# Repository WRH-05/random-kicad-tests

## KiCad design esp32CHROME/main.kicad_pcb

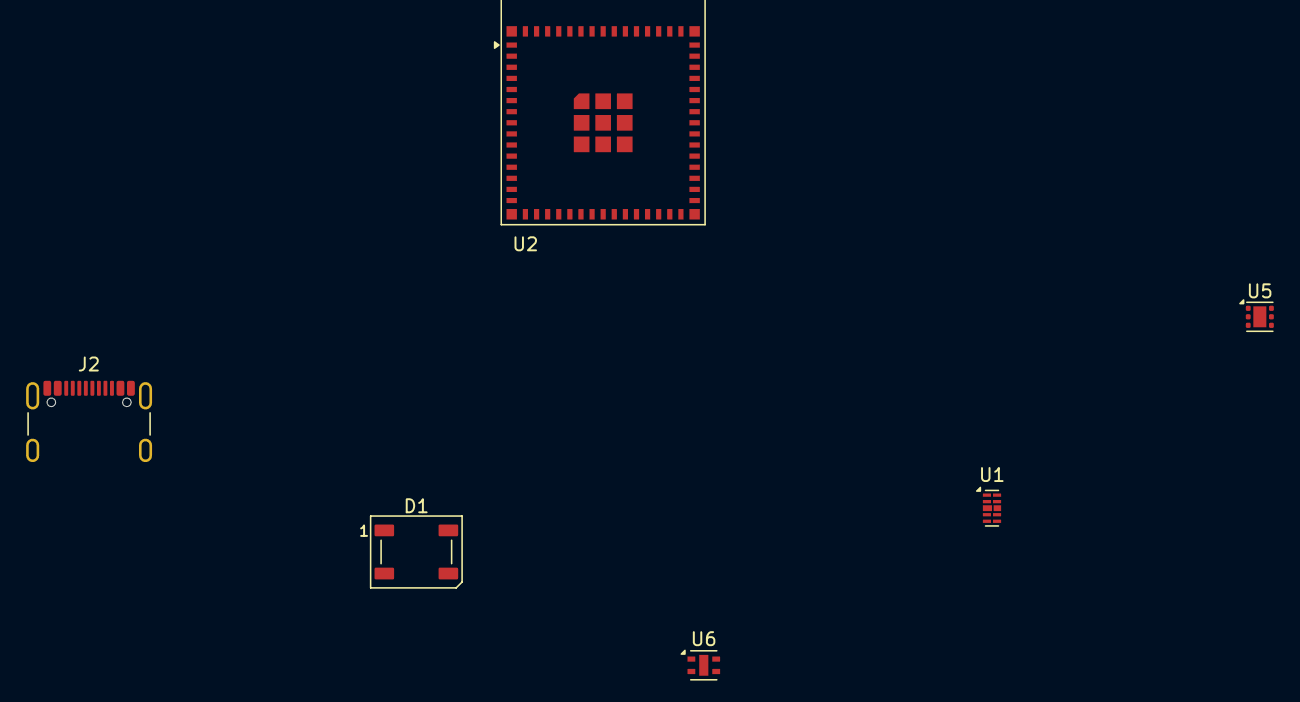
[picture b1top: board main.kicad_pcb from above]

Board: 2 copper layers, 6 parts (0 on the bottom side), 6 nets, no tracks yet.

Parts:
D1: WS2812B; LED_WS2812B_PLCC4_5.0x5.0mm_P3.2mm
J2: USB_C_Receptacle_USB2.0_16P; USB_C_Receptacle_GCT_USB4105-xx-A_16P_TopMnt_Horizontal
U1: D3V3XA4B10LP; Diodes_UDFN-10_1.0x2.5mm_P0.5mm
U2: ESP32-S3-MINI-1; ESP32-S2-MINI-1
U5: TLV75801PDRV; WSON-6-1EP_2x2mm_P0.65mm_EP1x1.6mm
U6: ENS210; AMS_QFN-4-1EP_2x2mm_P0.95mm_EP0.7x1.6mm

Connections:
unnamed: J2.A1 (GND), J2.A12 (GND), J2.B1 (GND), J2.B12 (GND)
unnamed: J2.A4 (VBUS), J2.A9 (VBUS), J2.B4 (VBUS), J2.B9 (VBUS)
unnamed: U1.3 (VSS), U1.8 (VSS)
unnamed: U2.1 (GND), U2.2 (GND), U2.42 (GND), U2.43 (GND), U2.46 (GND), U2.47 (GND), U2.48 (GND), U2.49 (GND), U2.50 (GND), U2.51 (GND), U2.52 (GND), U2.53 (GND), U2.54 (GND), U2.55 (GND), U2.56 (GND), U2.57 (GND), U2.58 (GND), U2.59 (GND), U2.60 (GND), U2.61 (GND), U2.62 (GND), U2.63 (GND), U2.64 (GND), U2.65 (GND)
unnamed: U5.3 (GND), U5.7 (GND)
unnamed: U6.4 (GND), U6.5 (GND)

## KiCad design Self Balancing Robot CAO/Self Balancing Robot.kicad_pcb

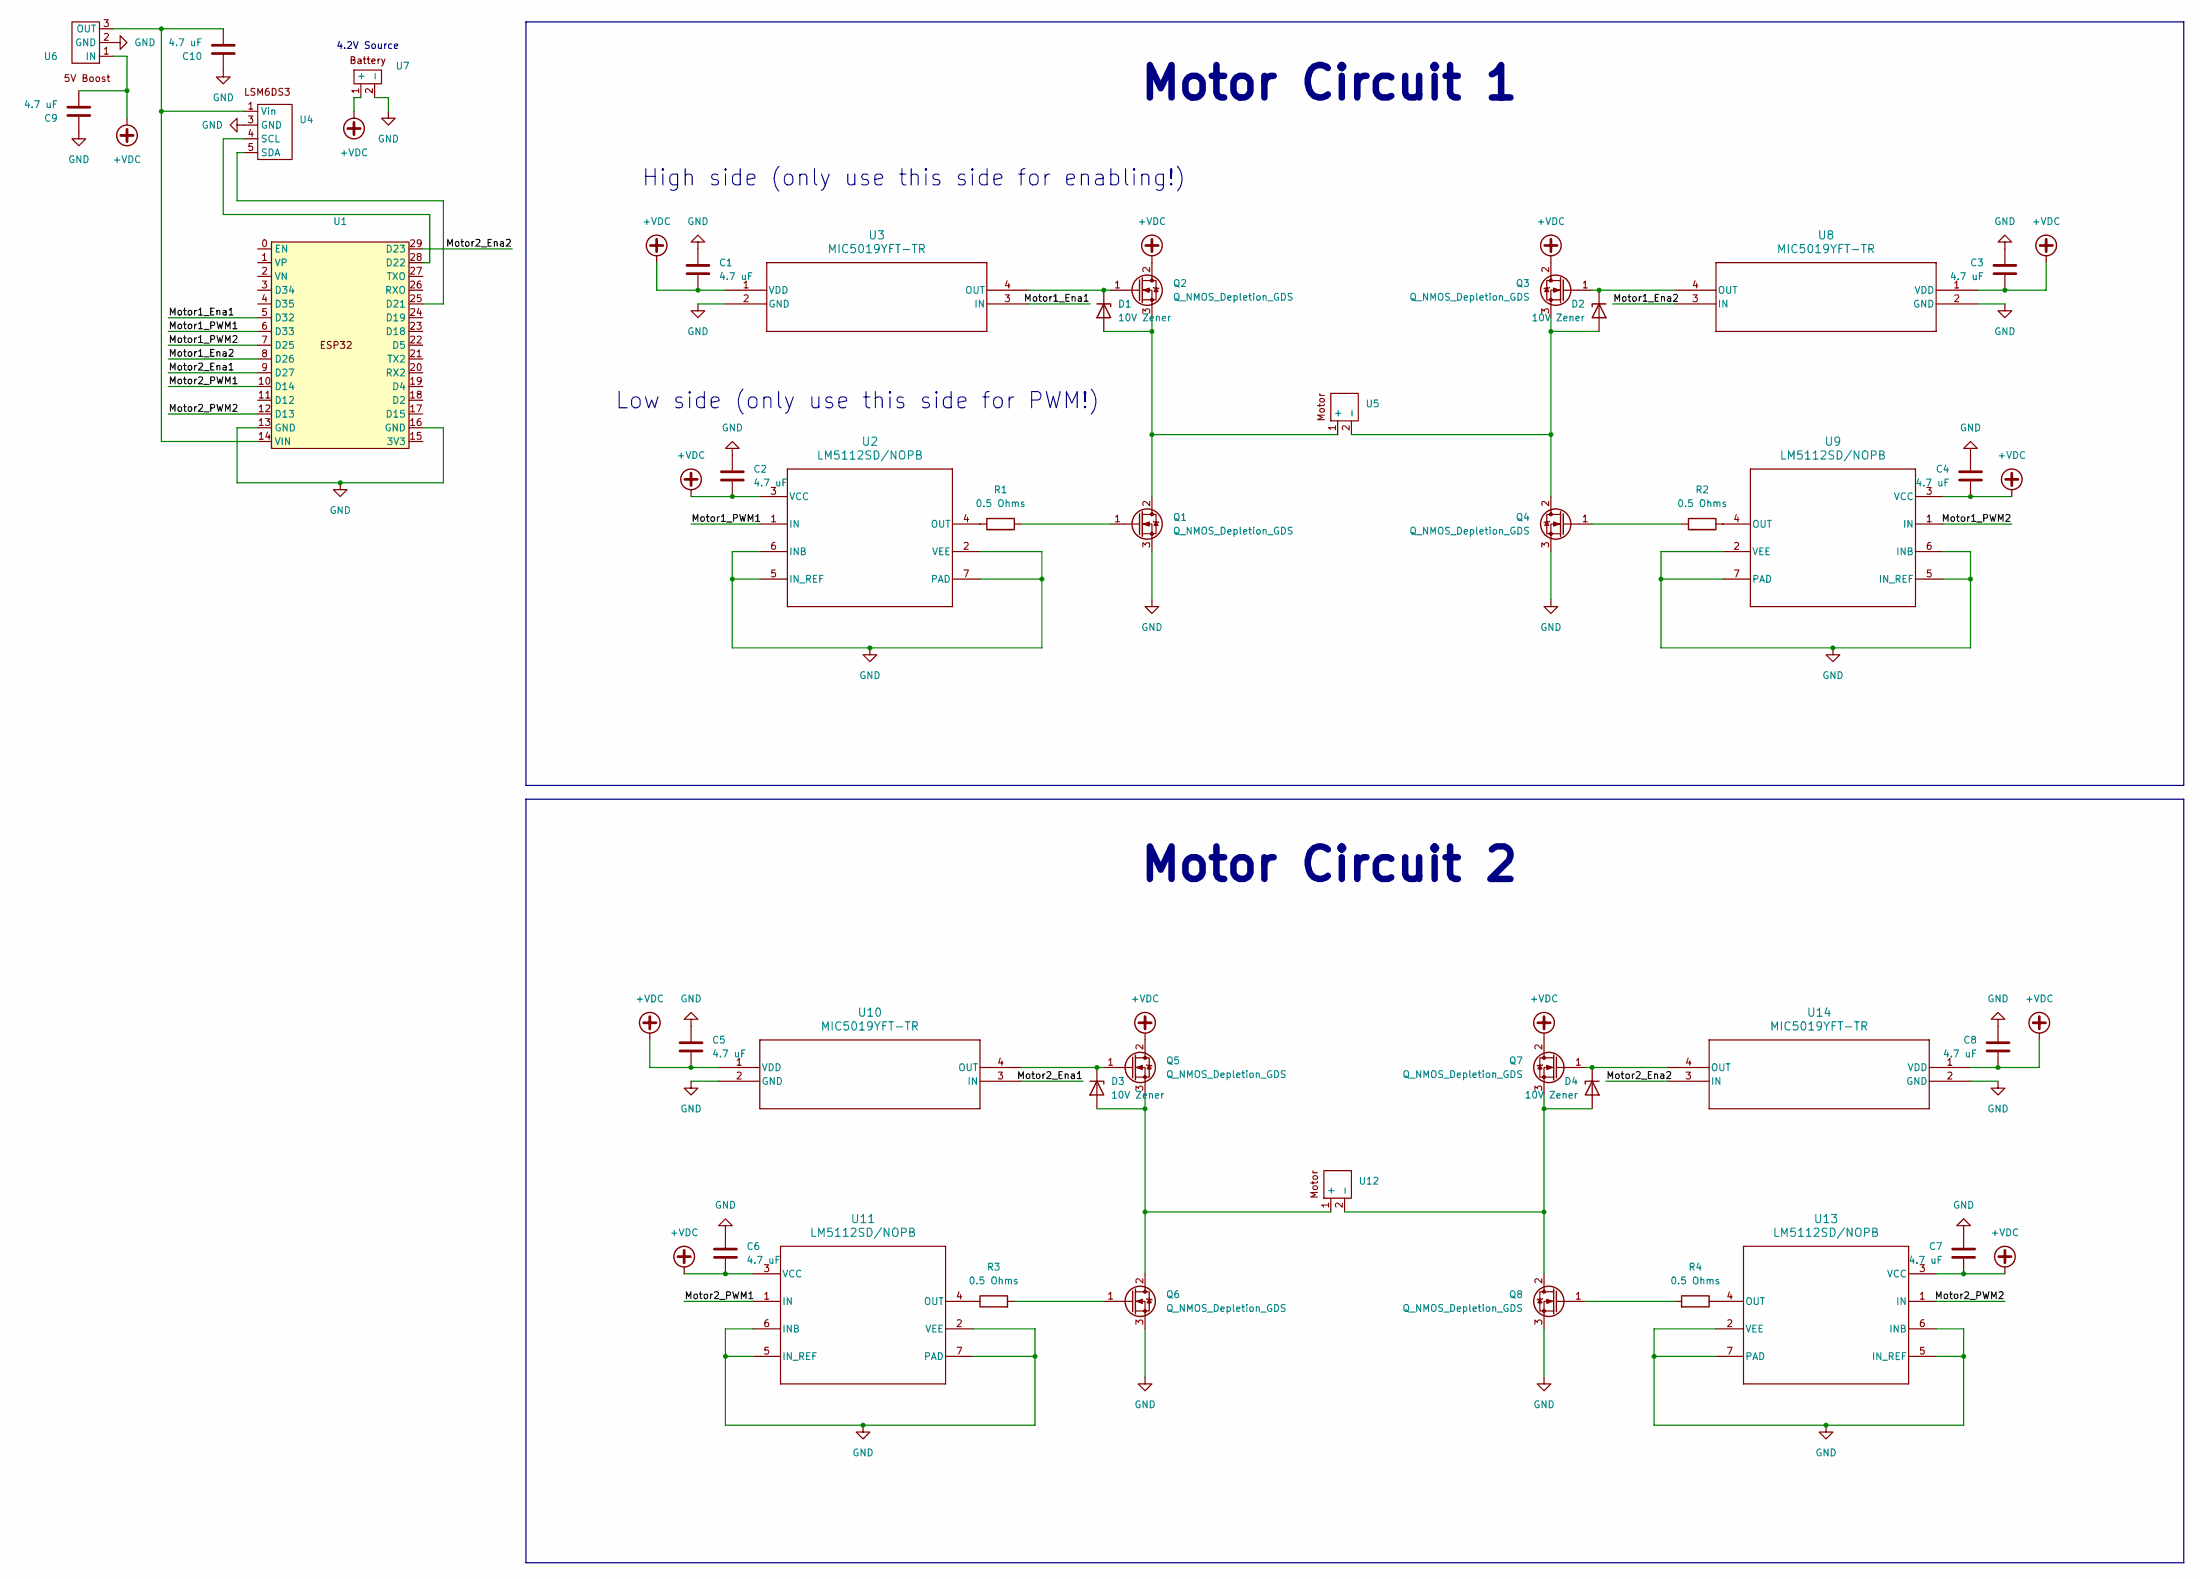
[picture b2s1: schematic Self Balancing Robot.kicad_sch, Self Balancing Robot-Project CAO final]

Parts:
C1, C2, C3, C4, C5, C6, C7, C8, C9, C10: 4.7 uF; C_0805_2012Metric_Pad1.18x1.45mm_HandSolder
D1, D2, D3, D4: 10V Zener; TSOT-23
Q1, Q2, Q3, Q4, Q5, Q6, Q7, Q8: Q_NMOS_Depletion_GDS; TO-252-2
R1, R2, R3, R4: 0.5 Ohms; R_2010_5025Metric_Pad1.40x2.65mm_HandSolder
U1: ESP32
U2, U9, U11, U13: LM5112SD/NOPB; LM5112SD
U3, U8, U10, U14: MIC5019YFT-TR
U4: LSM6DS3
U5, U12: Motor
U6: Boost
U7: Battery

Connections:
+VDC: C1.2, C2.2, C3.2, C4.2, C5.2, C6.2, C7.2, C8.2, C9.2, Q2.2 (D), Q3.2 (D), Q5.2 (D), Q7.2 (D), U2.3 (VCC), U3.1 (VDD), U6.1 (IN), U7.1 (+), U8.1 (VDD), U9.3 (VCC), U10.1 (VDD), U11.3 (VCC), U13.3 (VCC), U14.1 (VDD)
/Motor1_Ena1: U1.5 (D32), U3.3 (IN)
/Motor1_Ena2: U1.8 (D26), U8.3 (IN)
/Motor1_PWM1: U1.6 (D33), U2.1 (IN)
/Motor1_PWM2: U1.7 (D25), U9.1 (IN)
/Motor2_Ena1: U1.9 (D27), U10.3 (IN)
/Motor2_Ena2: U1.29 (D23), U14.3 (IN)
/Motor2_PWM1: U1.10 (D14), U11.1 (IN)
/Motor2_PWM2: U1.12 (D13), U13.1 (IN)
GND: C1.1, C2.1, C3.1, C4.1, C5.1, C6.1, C7.1, C8.1, C9.1, C10.1, Q1.3 (S), Q4.3 (S), Q6.3 (S), Q8.3 (S), U1.13 (GND), U1.16 (GND), U2.2 (VEE), U2.5 (IN_REF), U2.6 (INB), U2.7 (PAD), U3.2 (GND), U4.3 (GND), U6.2 (GND), U7.2 (-), U8.2 (GND), U9.2 (VEE), U9.5 (IN_REF), U9.6 (INB), U9.7 (PAD), U10.2 (GND), U11.2 (VEE), U11.5 (IN_REF), U11.6 (INB), U11.7 (PAD), U13.2 (VEE), U13.5 (IN_REF), U13.6 (INB), U13.7 (PAD), U14.2 (GND)
unnamed: D1.1 (A), Q1.2 (D), Q2.3 (S), U5.1 (+)
unnamed: D1.3 (K), Q2.1 (G), U3.4 (OUT)
unnamed: D2.1 (A), Q3.3 (S), Q4.2 (D), U5.2 (-)
unnamed: D2.3 (K), Q3.1 (G), U8.4 (OUT)
unnamed: D3.1 (A), Q5.3 (S), Q6.2 (D), U12.1 (+)
unnamed: D3.3 (K), Q5.1 (G), U10.4 (OUT)
unnamed: D4.1 (A), Q7.3 (S), Q8.2 (D), U12.2 (-)
unnamed: D4.3 (K), Q7.1 (G), U14.4 (OUT)
unnamed: Q1.1 (G), R1.2
unnamed: Q4.1 (G), R2.2
unnamed: Q6.1 (G), R3.2
unnamed: Q8.1 (G), R4.2
unnamed: U1.25 (D21), U4.5 (SDA)
unnamed: U1.28 (D22), U4.4 (SCL)
unnamed: C10.2, U1.14 (VIN), U4.1 (Vin), U6.3 (OUT)
unnamed: R1.1, U2.4 (OUT)
unnamed: R2.1, U9.4 (OUT)
unnamed: R3.1, U11.4 (OUT)
unnamed: R4.1, U13.4 (OUT)

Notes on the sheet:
4.2V Source
Motor Circuit 2
Motor Circuit 1
High side (only use this side for enabling!)
Low side (only use this side for PWM!)

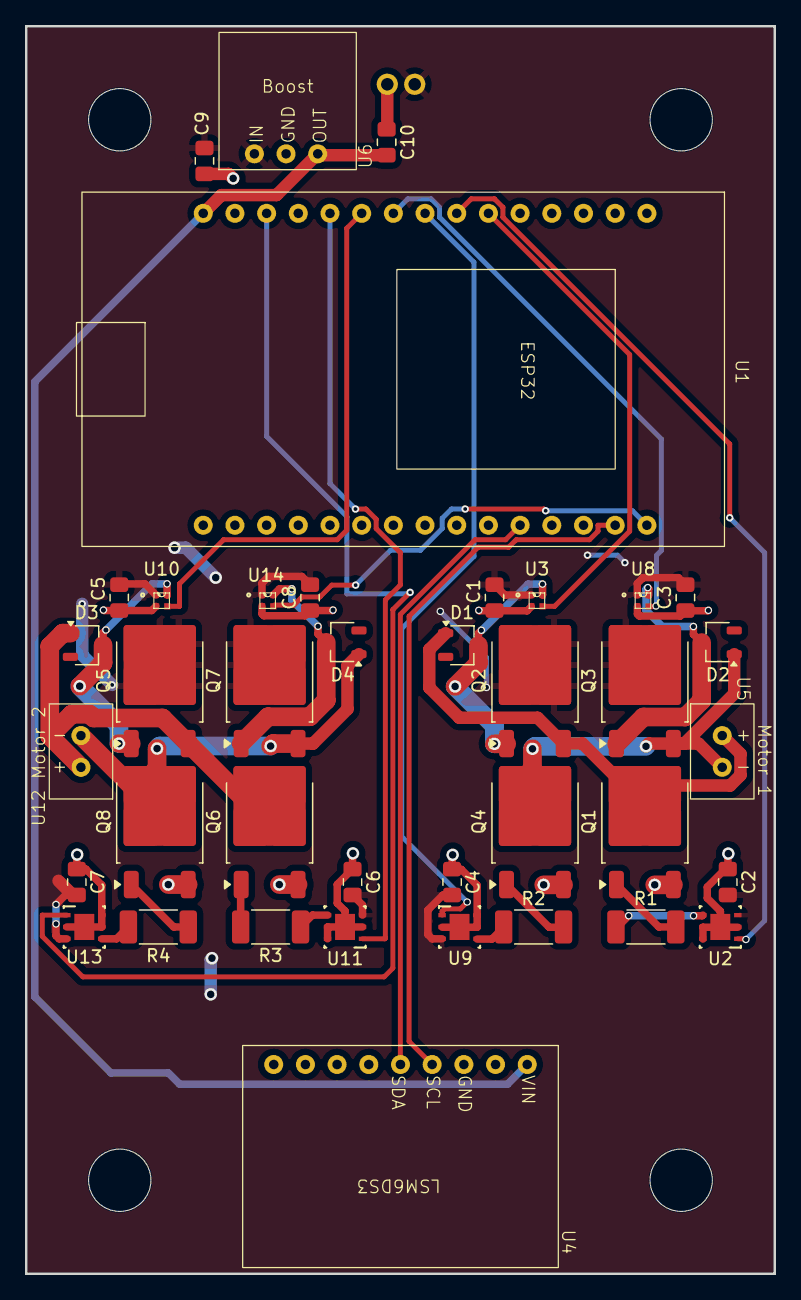
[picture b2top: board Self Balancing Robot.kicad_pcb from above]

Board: 2 copper layers, 60.0 x 100.0 mm, 40 parts (1 on the bottom side), 29 nets.

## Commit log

2025-09-24 first commit making kicad pcb test public
2025-09-24 esp32 setup
2025-09-24 initialization
2025-09-26 forgot what i changed from yesterday doesn't matter anyways
2025-09-29 added main components for the custom esp32 full integration
